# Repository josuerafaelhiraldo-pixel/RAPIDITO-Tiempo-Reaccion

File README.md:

# RAPIDITO [Tiempo-Reacción]

Diseño de proyecto – Electiva (Mecatrónica)

RAPIDITO es un proyecto orientado a la enseñanza práctica de microcontroladores. El sistema genera estímulos **visuales (LED)** y **auditivos (buzzer)**, y mide con alta precisión el **tiempo de reacción** del usuario desde que se emite el estímulo hasta que presiona el botón de respuesta. La medición, en milisegundos o microsegundos, se envía por conexión inalámbrica a una **aplicación móvil** que la muestra y la analiza.

## Cómo funciona

1. El usuario elige en la app el tipo de estímulo (LED, buzzer o ambos).
2. El ESP32 espera un intervalo aleatorio y activa el estímulo. Al mismo tiempo inicia un **timer de hardware**.
3. Al presionar el botón, una **interrupción (ISR)** detiene el conteo de inmediato.
4. El ESP32 envía el tiempo medido a la app, que lo muestra y lo compara con rangos de referencia.

## Componentes

| Parte | Descripción |
|---|---|
| Microcontrolador | ESP32 (comunicación inalámbrica con la app) |
| Estímulo visual | LED ultrabrillante |
| Estímulo sonoro | Buzzer |
| Entrada | Pulsador con filtro antirrebote |
| App móvil | Configuración de la prueba, resultados y gráfico |

## Estructura del repositorio

```
├── doc/             Documentación (Especificación de requisitos IEEE-830)
├── hardware/kicad/  Esquemático y diseño del circuito (KiCad)
├── mecanica/        Diseño mecánico (boceto de la carcasa)
├── LICENSE          Licencia MIT
└── README.md
```

## Documentación

La especificación de requisitos de software y hardware, basada en el estándar **IEEE Std 830-1998**, está en la carpeta [`doc/`](doc/).

## Equipo

| Integrante | Rol |
|---|---|
| Juan Eduardo Vasquez Pilier | Fundador / representante del equipo |
| Dioni Markin Hernandez | Desarrollador de firmware y analista de cálculo |
| Josué Rafael Hiraldo Fajardo | Desarrollador de la app y encargado del repositorio |
| Rafael Ovalles | Ingeniero de electrónica |
| Luismel Pinales Santana | Diseñador gráfico y de interfaz (UI/UX) |

## Obtener el proyecto

```bash
git clone https://github.com/josuerafaelhiraldo-pixel/RAPIDITO-Tiempo-Reaccion.git
cd RAPIDITO-Tiempo-Reaccion
```

## Audiencia

- **Docente:** validación del cumplimiento funcional y educativo.
- **Estudiantes / usuarios finales:** comprender la interacción con el sistema.

## Licencia

Distribuido bajo licencia MIT. Ver el archivo [LICENSE](LICENSE).

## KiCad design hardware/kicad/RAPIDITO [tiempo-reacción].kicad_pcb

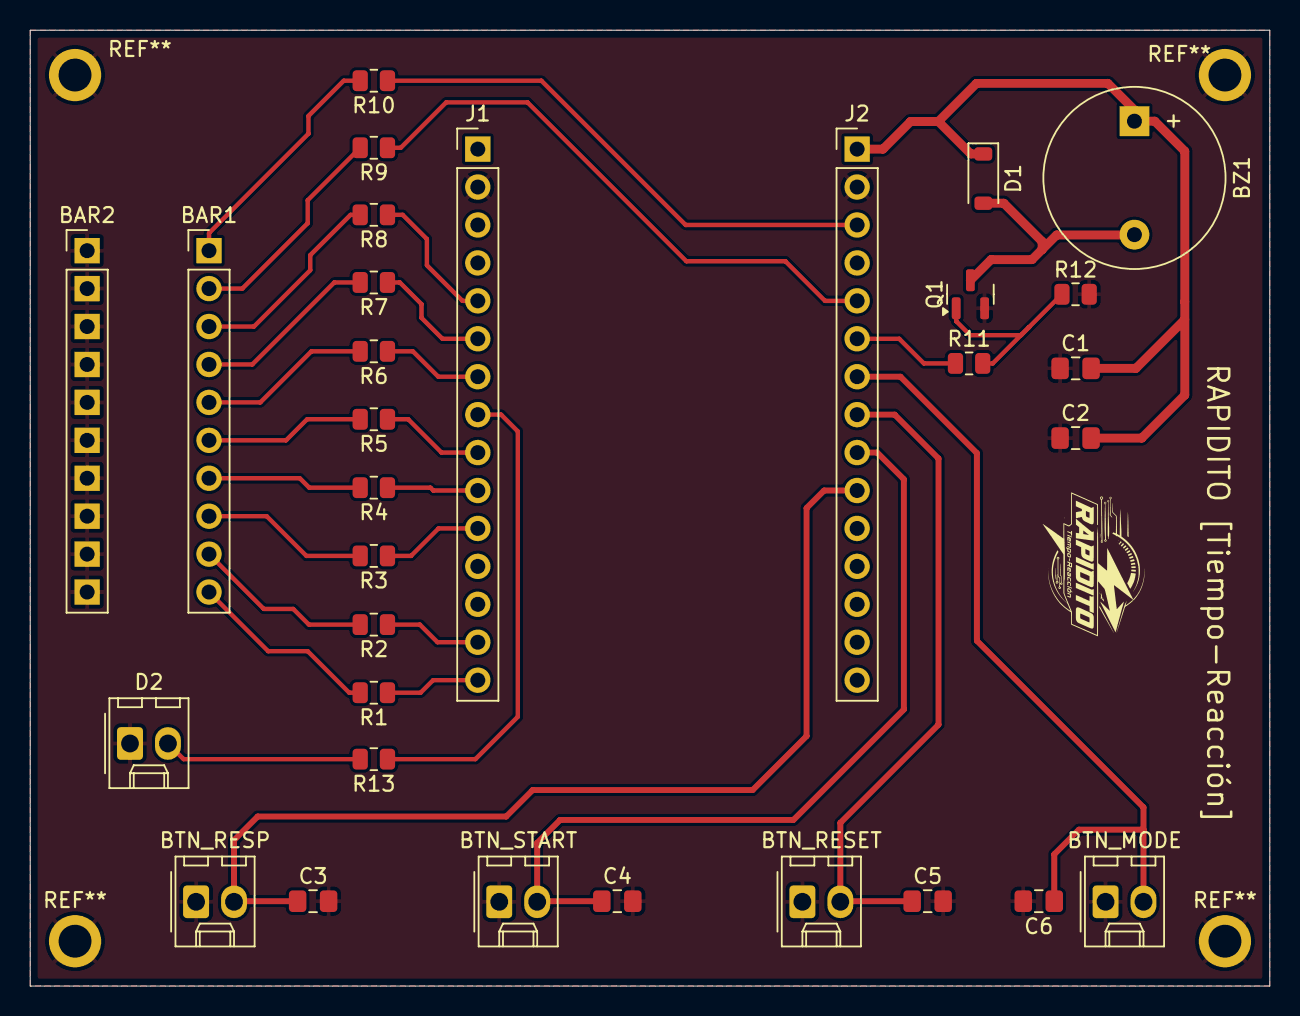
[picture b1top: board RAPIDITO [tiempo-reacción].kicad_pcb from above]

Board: 2 copper layers, 83.0 x 64.0 mm, 31 parts (0 on the bottom side), 31 nets.

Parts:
BAR1, BAR2: HDSP-4830_2; PinHeader_1x10_P2.54mm_Vertical
BTN_MODE: PB4; Molex_KK-254_AE-6410-02A_1x02_P2.54mm_Vertical
BTN_RESET: PB3; Molex_KK-254_AE-6410-02A_1x02_P2.54mm_Vertical
BTN_RESP: PB1; Molex_KK-254_AE-6410-02A_1x02_P2.54mm_Vertical
BTN_START: PB2; Molex_KK-254_AE-6410-02A_1x02_P2.54mm_Vertical
BZ1: Buzzer; Buzzer_12x9.5RM7.6
C1: 100nF; C_0805_2012Metric_Pad1.18x1.45mm_HandSolder
C2: 10µF; C_0805_2012Metric_Pad1.18x1.45mm_HandSolder
C3, C4, C5, C6: 22nF; C_0805_2012Metric_Pad1.18x1.45mm_HandSolder
D1: 1N4148W; D_SOD-123
D2: LED; Molex_KK-254_AE-6410-02A_1x02_P2.54mm_Vertical
J1, J2: Screw_Terminal_01x15; PinHeader_1x15_P2.54mm_Vertical
Q1: MMBT3904; SOT-23
R1, R2, R3, R4, R5, R6, R7, R8, R9, R10, R13: 330Ω; R_0805_2012Metric
R11: 1kΩ; R_0805_2012Metric
R12: 10kΩ; R_0805_2012Metric

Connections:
+5V: BZ1.1 (+), C1.2, C2.2, D1.1 (K), J2.1
BUZZER: J2.6, R11.1
GND: BAR2.1 (A), BAR2.2 (A), BAR2.3 (A), BAR2.4 (A), BAR2.5 (A), BAR2.6 (A), BAR2.7 (A), BAR2.8 (A), BAR2.9 (A), BAR2.10 (A), BTN_MODE.1, BTN_RESET.1, BTN_RESP.1, BTN_START.1, C1.1, C2.1, C3.2, C4.2, C5.2, C6.2, D2.1 (K), J1.2, J2.2, Q1.2 (E), R12.2
LED1: J1.15, R1.1
LED2: J1.14, R2.1
LED3: J1.11, R3.1
LED4: J1.10, R4.1
LED5: J1.9, R5.1
LED6: J1.7, R6.1
LED7: J1.6, R7.1
LED8: J1.5, R8.1
LED9: J2.5, R9.1
LED10: J2.3, R10.1
LED_MODE: J1.8, R13.1
MODE_input: BTN_MODE.2, C6.1, J2.7
unnamed: BAR1.1 (A), R10.2
unnamed: BAR1.2 (A), R9.2
unnamed: BAR1.3 (A), R8.2
unnamed: BAR1.4 (A), R7.2
unnamed: BAR1.5 (A), R6.2
unnamed: BAR1.6 (A), R5.2
unnamed: BAR1.7 (A), R4.2
unnamed: BAR1.8 (A), R3.2
unnamed: BAR1.9 (A), R2.2
unnamed: BAR1.10 (A), R1.2
unnamed: BZ1.2 (-), D1.2 (A), Q1.3 (C)
unnamed: D2.2 (A), R13.2
unnamed: Q1.1 (B), R11.2, R12.1
RESET_input: BTN_RESET.2, C5.1, J2.8
RESP_input: BTN_RESP.2, C3.1, J2.10
START_input: BTN_START.2, C4.1, J2.9
